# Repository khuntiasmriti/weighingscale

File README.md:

# Digital Weighing Scale (Pre-Alpha)

## Overview

One day, after returning home from the hostel for the holidays, I found myself stepping onto an old weighing scale after eating far more than I probably should have. While staring at the number it displayed, a question popped into my head: **How does this machine know my weight so accurately?** The question disappeared as quickly as it arrived, only to return when I watched a coffee enthusiast using a precision scale capable of measuring coffee grounds to two decimal places. That curiosity led me down a rabbit hole of strain gauges, load cells, Wheatstone bridges, and signal conditioning. This project is my attempt to understand how a modern digital weighing scale works by designing one from scratch.

This repository is my attempt to understand how a digital weighing scale works by studying its sensing chain, selecting the required components, and beginning the PCB design process. At its current stage, this project is just hardware planning.

---

## Project Goal

The purpose of this project is to understand how force can be converted into a measurable electrical signal and eventually into a digital output.

This project currently explores:

* Strain gauge technology
* Load cell operation
* Wheatstone bridge fundamentals
* Signal amplification using HX711
* Embedded system architecture
* Power regulation
* PCB planning in KiCad

---

## Current Stage

This project is currently in **pre-alpha**.

What has been done so far:

* Researched the working principle of digital weighing scales
* Studied strain gauge and load cell operation
* Selected all major components
* Defined the complete sensing chain
* Started the PCB schematic layout in KiCad

What has **not** been done yet:

* Component interconnections are incomplete
* PCB routing has not started
* BOM has not been generated
* STM32 firmware has not been written
* Calibration routines have not been implemented
* Simulation and hardware testing have not been performed

---

## Proposed System Architecture

```text
Weight Applied
      ↓
20 kg Single-Point Load Cell
      ↓
Wheatstone Bridge Output
      ↓
HX711 Load Cell Amplifier
      ↓
STM32F103C8T6 Microcontroller
      ↓
0.96" OLED Display
```

---

## Selected Components

### 20 kg Single-Point Load Cell
Chosen as the primary force sensing element. The load cell contains strain gauges arranged in a Wheatstone bridge configuration, producing a small differential voltage when deformed.

### HX711 Load Cell Amplifier
Selected for:
* High precision amplification
* 24-bit ADC conversion
* Easy microcontroller interfacing

This component is essential because the load cell output is too small to be directly processed.

### STM32F103C8T6
Chosen because of prior familiarity with the Blue Pill platform.
Responsibilities will include:
* Reading HX711 output
* Processing weight values
* Handling display communication
* Future filtering and calibration

### 0.96" OLED Display
Chosen as the output interface. Will communicate over I²C. Mostly because I wanted to use my I²C knowledge properly for once.

### Power Section

Planned:
* USB-C input (5V)
* AMS1117 3.3V regulator

To provide stable operating voltage for the system.

## Planned Development Roadmap

### Phase 1

* Complete schematic connections
* Verify circuit integrity
* Generate BOM

### Phase 2

* Finish PCB layout
* Perform ERC and DRC checks
* Prepare fabrication files

### Phase 3

* Write STM32 firmware
* Interface HX711
* Interface OLED

### Phase 4

* Implement calibration
* Add tare functionality
* Add filtering

### Phase 5

* Fabricate and test hardware

---

## Limitations

At this stage, this project is only a design and research exercise. It does not yet function as a working weighing scale. No physical or software validation has been performed yet.

---

## Author's Note

This repository is less about building something perfect and more about understanding how an everyday device works. Right now, this is mostly curiosity, component selection, half-baked knowledge from five odd seniors and unfinished wires.

But every project starts there.

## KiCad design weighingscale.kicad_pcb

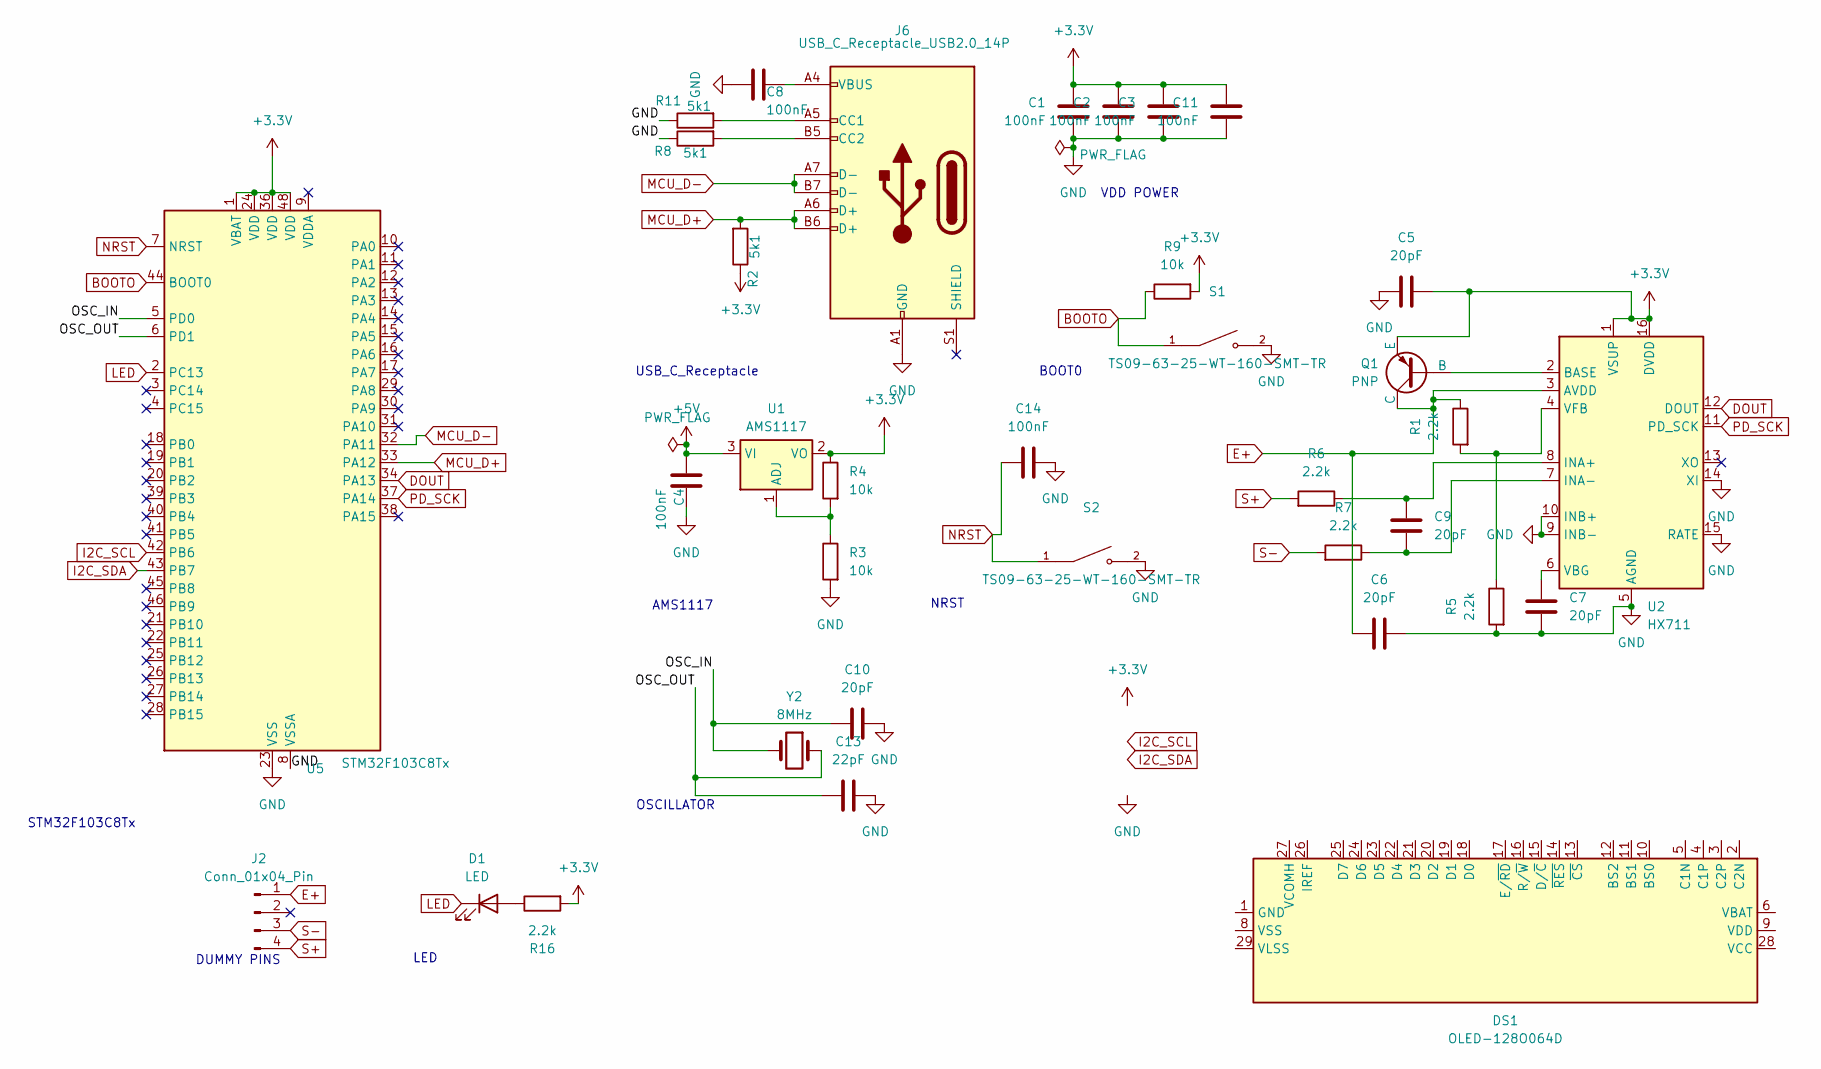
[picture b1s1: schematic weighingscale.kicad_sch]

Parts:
C1, C2, C3, C4, C8, C11, C14: 100nF; C_0603_1608Metric_Pad1.08x0.95mm_HandSolder
C5, C6, C7, C9, C10: 20pF; C_0603_1608Metric_Pad1.08x0.95mm_HandSolder
C13: 22pF; C_0603_1608Metric_Pad1.08x0.95mm_HandSolder
D1: LED; LED_0603_1608Metric_Pad1.05x0.95mm_HandSolder
DS1: OLED-128O064D
J2: Conn_01x04_Pin; PinSocket_1x04_P2.00mm_Vertical
J6: USB_C_Receptacle_USB2.0_14P; USB_C_Receptacle_GCT_USB4105-xx-A_16P_TopMnt_Horizontal
Q1: PNP; SOT-457T
R1, R5, R6, R7, R16: 2.2k; R_0603_1608Metric_Pad0.98x0.95mm_HandSolder
R2, R8, R11: 5k1; R_0603_1608Metric_Pad0.98x0.95mm_HandSolder
R3, R4, R9: 10k; R_0603_1608Metric_Pad0.98x0.95mm_HandSolder
S1, S2: TS09-63-25-WT-160-SMT-TR; SW_TS09-63-25-WT-160-SMT-TR; PARTREV 1.0
U1: AMS1117; SOT-223-3_TabPin2
U2: HX711; SOIC-16_3.9x9.9mm_P1.27mm
U5: STM32F103C8Tx; LQFP-48_7x7mm_P0.5mm
Y2: 8MHz; Crystal_SMD_HC49-SD

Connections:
+3.3V: C1.1, C2.1, C3.1, C5.2, C11.1, Q1.3 (E), R2.1, R4.1, R9.2, R16.2, U1.2 (VO), U2.1 (VSUP), U2.16 (DVDD), U5.1 (VBAT), U5.24 (VDD), U5.36 (VDD), U5.48 (VDD); also elsewhere on the board
+5V: C4.1, U1.3 (VI)
/OSC_IN: C10.2, U5.5 (PD0), Y2.2
/OSC_OUT: C13.2, U5.6 (PD1), Y2.1
BOOTO: R9.1, S1.1, U5.44 (BOOT0)
DOUT: U2.12 (DOUT), U5.34 (PA13)
E+: C6.1, J2.1, Q1.1 (C), R1.1, U2.3 (AVDD)
GND: C1.2, C2.2, C3.2, C4.2, C5.1, C6.2, C7.2, C8.1, C10.1, C11.2, C13.1, C14.1, J6.A1 (GND), J6.A12 (GND), J6.B1 (GND), J6.B12 (GND), R3.2, R5.2, R8.1, R11.1, S1.2, S2.2, U2.5 (AGND), U2.9 (INB-), U2.10 (INB+), U2.14 (XI), U2.15 (RATE), U5.8 (VSSA), U5.23 (VSS), U5.35 (VSS), U5.47 (VSS); also elsewhere on the board
I2C_SCL: U5.42 (PB6); also elsewhere on the board
I2C_SDA: U5.43 (PB7); also elsewhere on the board
LED: D1.1 (K), U5.2 (PC13)
MCU_D+: J6.A6 (D+), J6.B6 (D+), R2.2, U5.33 (PA12)
MCU_D-: J6.A7 (D-), J6.B7 (D-), U5.32 (PA11)
NRST: C14.2, S2.1, U5.7 (NRST)
unnamed: C8.2, J6.A4 (VBUS), J6.A9 (VBUS), J6.B4 (VBUS), J6.B9 (VBUS)
unnamed: D1.2 (A), R16.1
unnamed: DS1.1 (GND), DS1.30 (GND)
unnamed: J6.A5 (CC1), R11.2
unnamed: J6.B5 (CC2), R8.2
unnamed: Q1.2 (B), U2.2 (BASE)
unnamed: R3.1, R4.2, U1.1 (ADJ)
unnamed: C9.1, R6.1, U2.8 (INA+)
unnamed: C9.2, R7.1, U2.7 (INA-)
unnamed: C7.1, U2.6 (VBG)
unnamed: R1.2, R5.1, U2.4 (VFB)
PD_SCK: U2.11 (PD_SCK), U5.37 (PA14)
S+: J2.4, R6.2
S-: J2.3, R7.2

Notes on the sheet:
OSCILLATOR
STM32F103C8Tx
AMS1117
USB_C_Receptacle
BOOT0
NRST
DUMMY PINS
VDD POWER
LED

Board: 2 copper layers, 35 parts (29 on the bottom side), 27 nets, no tracks yet.

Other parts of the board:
U3: DM-OLED096-636; Adafruit_SSD1306

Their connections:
+3.3V: U3.2 (VCC_IN); also elsewhere on the board
GND: U3.1 (GND); also elsewhere on the board
I2C_SCL: U3.3 (SCL); also elsewhere on the board
I2C_SDA: U3.4 (SDA); also elsewhere on the board
